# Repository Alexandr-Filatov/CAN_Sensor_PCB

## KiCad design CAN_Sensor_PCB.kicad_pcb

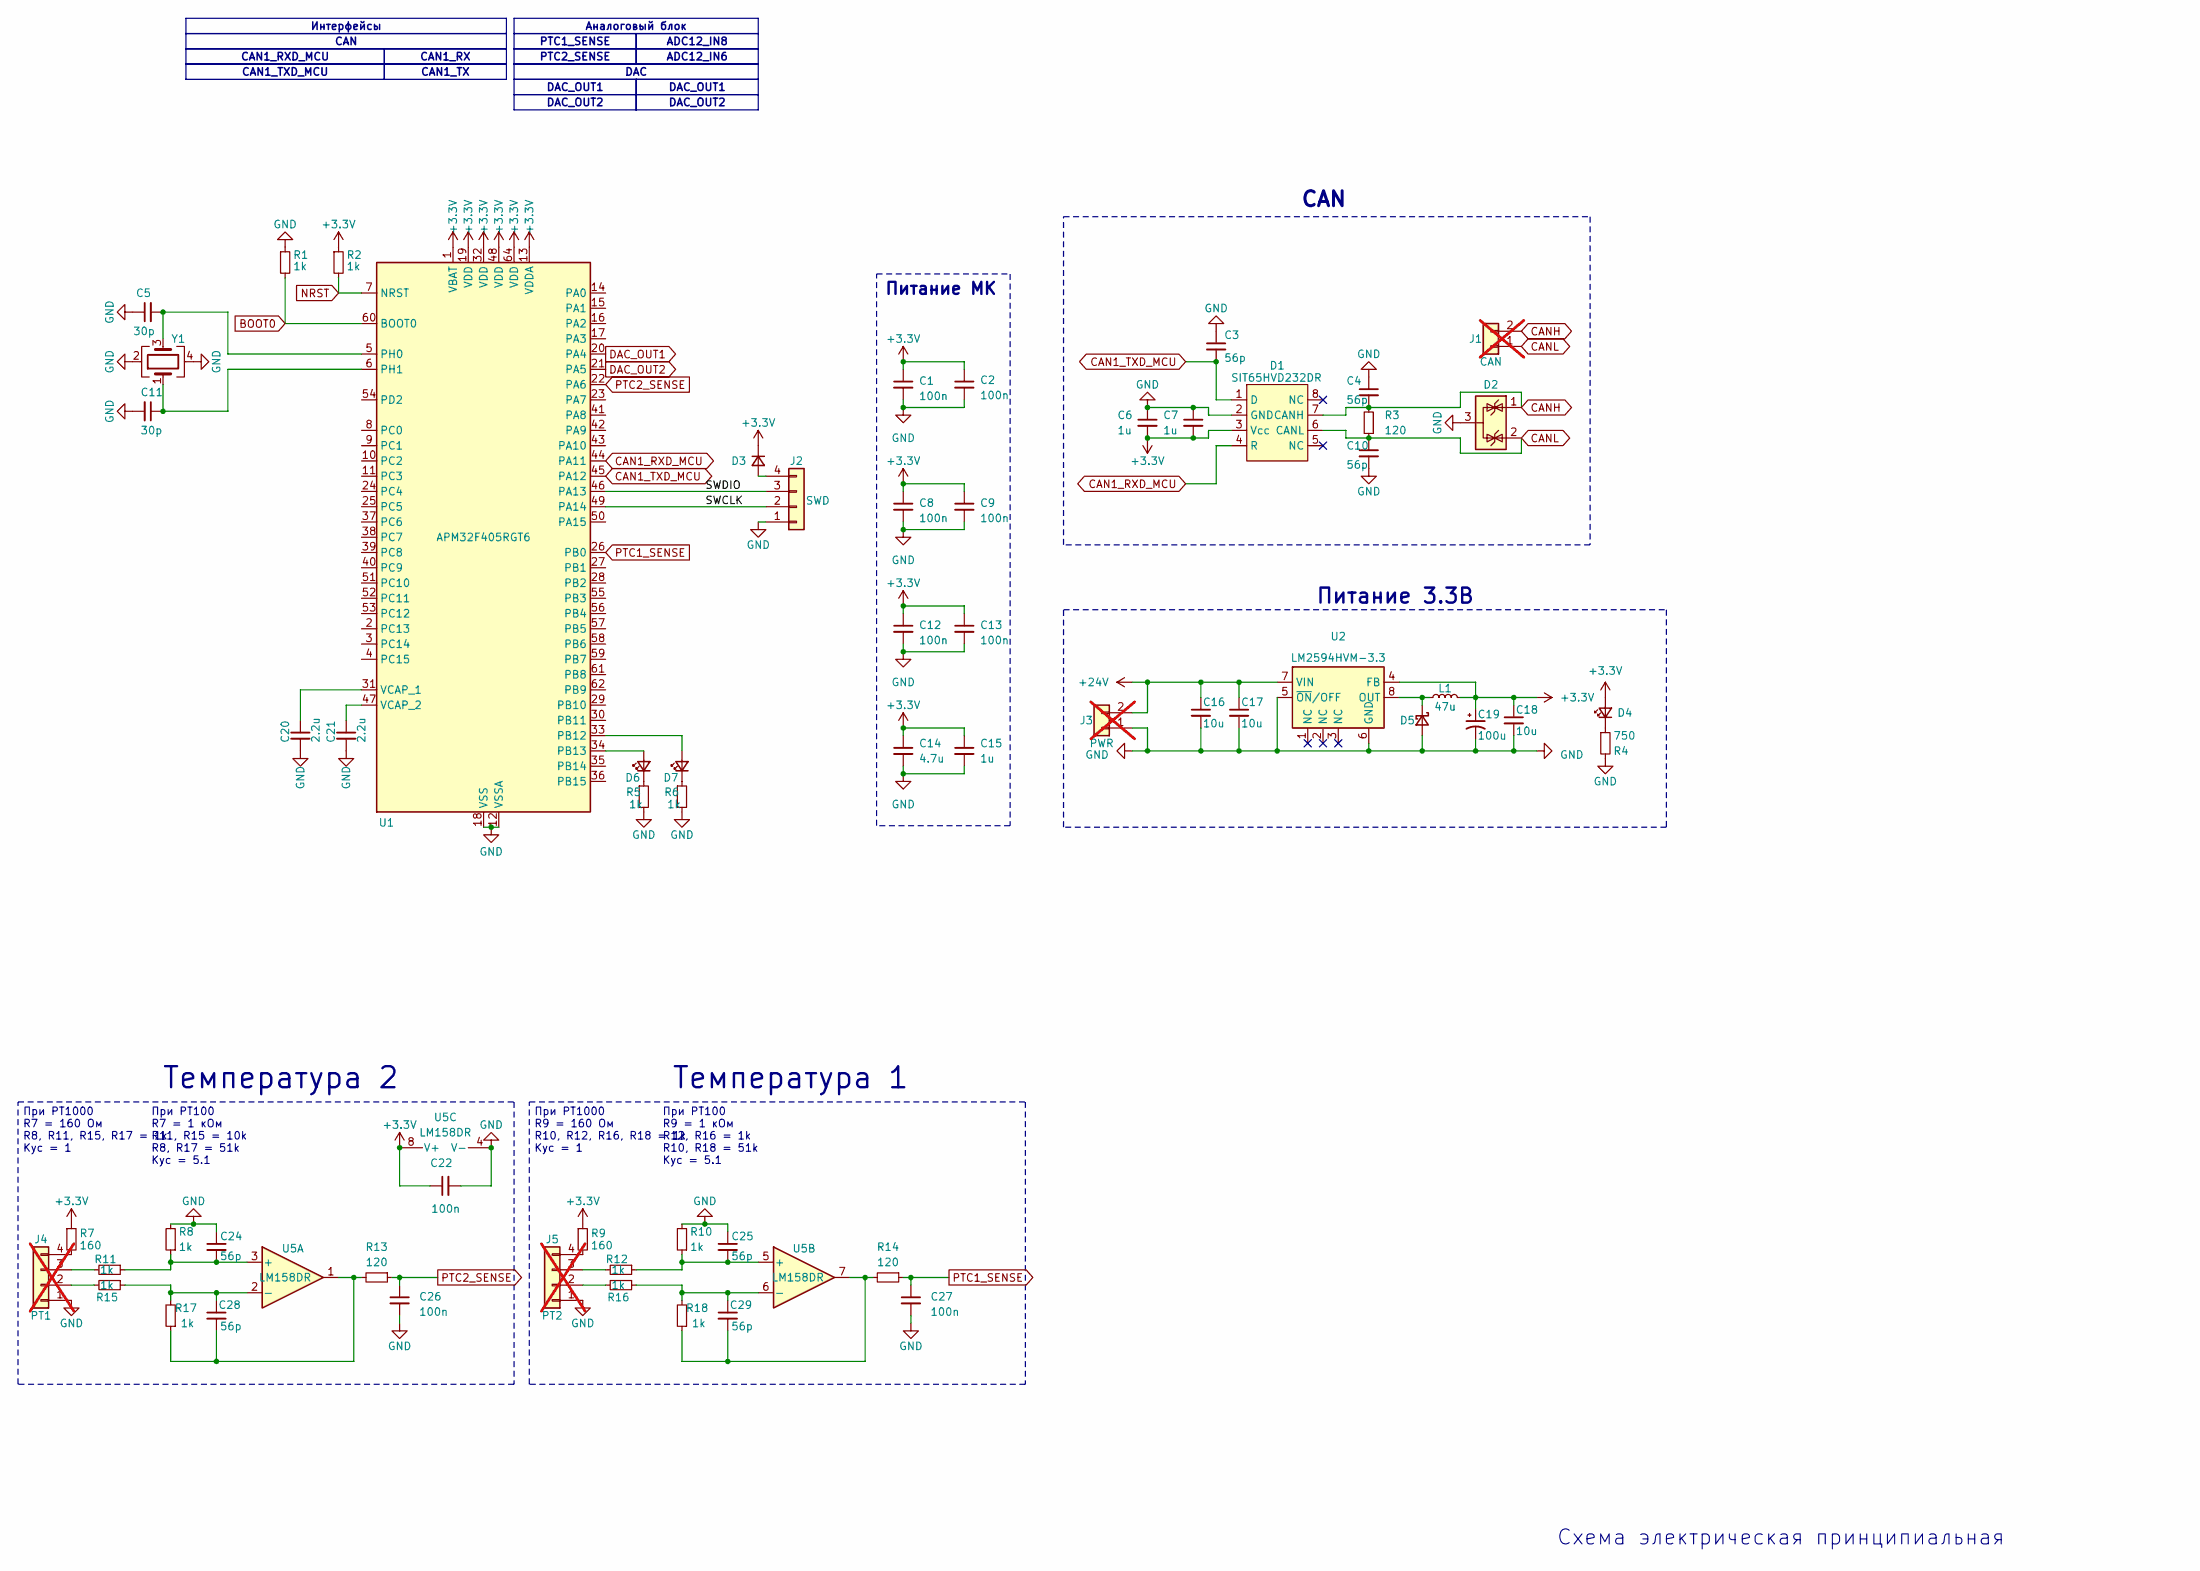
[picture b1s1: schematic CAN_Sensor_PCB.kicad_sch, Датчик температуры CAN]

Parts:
C1, C2, C8, C9, C12, C13, C22, C26, C27: 100n; C_0805_2012Metric_Pad1.18x1.45mm_HandSolder
C3, C4, C10, C24, C25, C28, C29: 56p; C_0805_2012Metric_Pad1.18x1.45mm_HandSolder
C5, C11: 30p; C_0805_2012Metric_Pad1.18x1.45mm_HandSolder
C6, C7, C15: 1u; C_0805_2012Metric_Pad1.18x1.45mm_HandSolder
C14: 4.7u; C_0805_2012Metric_Pad1.18x1.45mm_HandSolder
C16, C17, C18: 10u; C_1210_3225Metric_Pad1.33x2.70mm_HandSolder
C19: 100u; CP_EIA-3528-21_Kemet-B_HandSolder
C20, C21: 2.2u; C_0805_2012Metric_Pad1.18x1.45mm_HandSolder
D1: SOIC-8_3.9x4.9mm_P1.27mm
D2: SOT-23
D3: D_SOD-323_HandSoldering
D4, D6, D7: LED_0805_2012Metric
D5: D_SMA
J1, J3: Wire_1.5mm; not fitted
J2: PinHeader_1x04_P2.54mm_Vertical
J4, J5: Wire_1.5mm x 4; not fitted
L1: 47u; L_1812_4532Metric_Pad1.30x3.40mm_HandSolder
R1, R2, R5, R6, R8, R10, R11, R12, R15, R16, R17, R18: 1k; R_0805_2012Metric_Pad1.20x1.40mm_HandSolder
R3, R13, R14: 120; R_0805_2012Metric_Pad1.20x1.40mm_HandSolder
R4: 750; R_0805_2012Metric_Pad1.20x1.40mm_HandSolder
R7, R9: 160; R_0805_2012Metric_Pad1.20x1.40mm_HandSolder
U1: LQFP-64_10x10mm_P0.5mm
U2: SOIC-8_3.9x4.9mm_P1.27mm
U5: SO-8_3.9x4.9mm_P1.27mm
Y1: Crystal_SMD_SeikoEpson_FA238-4Pin_3.2x2.5mm

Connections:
+3.3V: C1.1, C2.1, C6.2, C7.2, C8.1, C9.1, C12.1, C13.1, C14.1, C15.1, C18.1, C19.1, C22.1, D1.3 (Vcc), D3.1 (K), D4.2 (A), L1.2, R2.1, R7.1, R9.1, U1.1 (VBAT), U1.13 (VDDA), U1.19 (VDD), U1.32 (VDD), U1.48 (VDD), U1.64 (VDD), U2.4 (FB), U5.8 (V+)
+24V: C16.1, C17.1, J3.2, U2.7 (VIN)
/SWCLK: J2.2, U1.49 (PA14)
/SWDIO: J2.3, U1.46 (PA13)
BOOT0: R1.2, U1.60 (BOOT0)
CAN1_RXD_MCU: D1.4 (R), U1.44 (PA11)
CAN1_TXD_MCU: C3.2, D1.1 (D), U1.45 (PA12)
CANH: C4.2, D1.7 (CANH), D2.1 (K), J1.2, R3.2
CANL: C10.1, D1.6 (CANL), D2.2 (K), J1.1, R3.1
DAC_OUT1: U1.20 (PA4)
DAC_OUT2: U1.21 (PA5)
GND: C1.2, C2.2, C3.1, C4.1, C5.1, C6.1, C7.1, C8.2, C9.2, C10.2, C11.2, C12.2, C13.2, C14.2, C15.2, C16.2, C17.2, C18.2, C19.2, C20.2, C21.2, C22.2, C24.1, C25.1, C26.2, C27.2, D1.2 (GND), D2.3 (A), D5.2 (A), J2.1, J3.1, J4.1, J5.1, R1.1, R4.2, R5.2, R6.2, R8.2, R10.2, U1.12 (VSSA), U1.18 (VSS), U1.63 (VSS), U2.5 (~ON/OFF), U2.6 (GND), U5.4 (V-), Y1.2, Y1.4
NRST: R2.2, U1.7 (NRST)
unnamed: C28.2, R13.2, R17.1, U5.1
unnamed: C29.2, R14.2, R18.1, U5.7
unnamed: D3.2 (A), J2.4
unnamed: D4.1 (K), R4.1
unnamed: D5.1 (K), L1.1, U2.8 (OUT)
unnamed: D6.2 (A), U1.34 (PB13)
unnamed: D6.1 (K), R5.1
unnamed: D7.2 (A), U1.33 (PB12)
unnamed: D7.1 (K), R6.1
unnamed: J4.2, R15.2
unnamed: J4.3, R11.2
unnamed: J4.4, R7.2
unnamed: J5.2, R16.2
unnamed: J5.3, R12.2
unnamed: J5.4, R9.2
unnamed: C5.2, U1.5 (PH0), Y1.3
unnamed: C11.1, U1.6 (PH1), Y1.1
unnamed: C20.1, U1.31 (VCAP_1)
unnamed: C21.1, U1.47 (VCAP_2)
unnamed: C24.2, R8.1, R11.1, U5.3 (+)
unnamed: C28.1, R15.1, R17.2, U5.2 (-)
unnamed: C25.2, R10.1, R12.1, U5.5 (+)
unnamed: C29.1, R16.1, R18.2, U5.6 (-)
PTC1_SENSE: C27.1, R14.1, U1.26 (PB0)
PTC2_SENSE: C26.1, R13.1, U1.22 (PA6)

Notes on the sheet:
Кус = 5.1
При PT1000
R10, R12, R16, R18 = 1k
R7 = 160 Ом
Схема электрическая принципиальная
R8, R17 = 51k
R9 = 160 Ом
Температура 2
R12, R16 = 1k
Питание МК
Температура 1
Питание 3.3В
R7 = 1 кОм
R9 = 1 кОм
R11, R15 = 10k
При PT100
CAN
Кус = 1
R10, R18 = 51k
R8, R11, R15, R17 = 1k
DAC_OUT2
CAN1_RX
DAC_OUT1
PTC1_SENSE
CAN1_TXD_MCU
CAN1_TX
DAC_OUT2
ADC12_IN6
PTC2_SENSE
CAN1_RXD_MCU
Интерфейсы
DAC
Аналоговый блок
ADC12_IN8

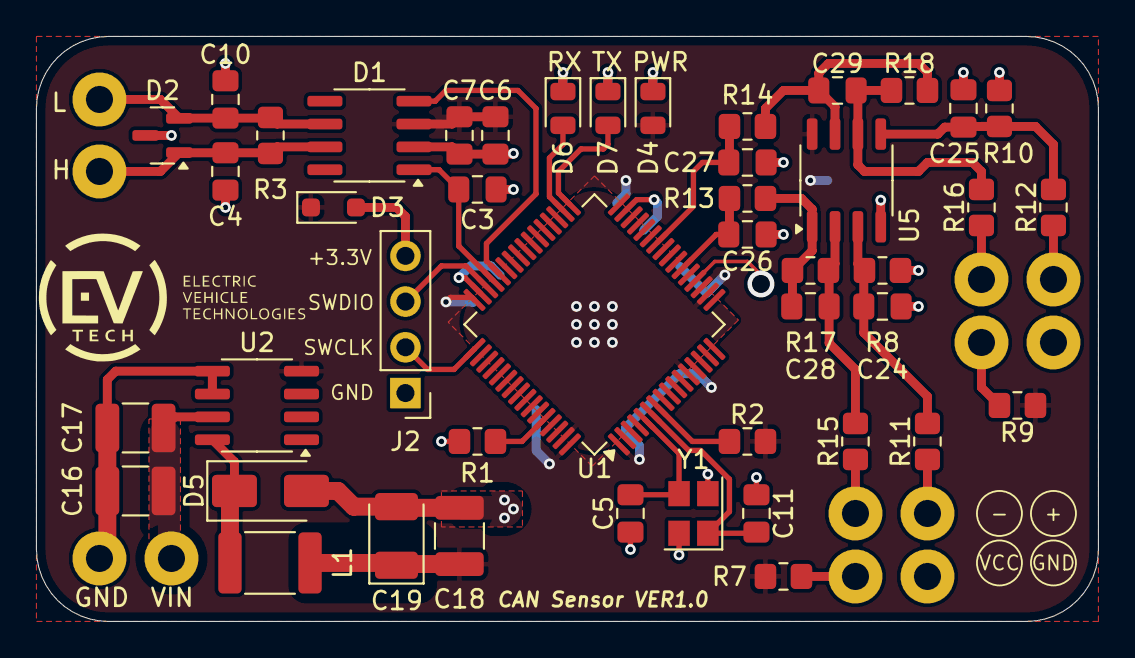
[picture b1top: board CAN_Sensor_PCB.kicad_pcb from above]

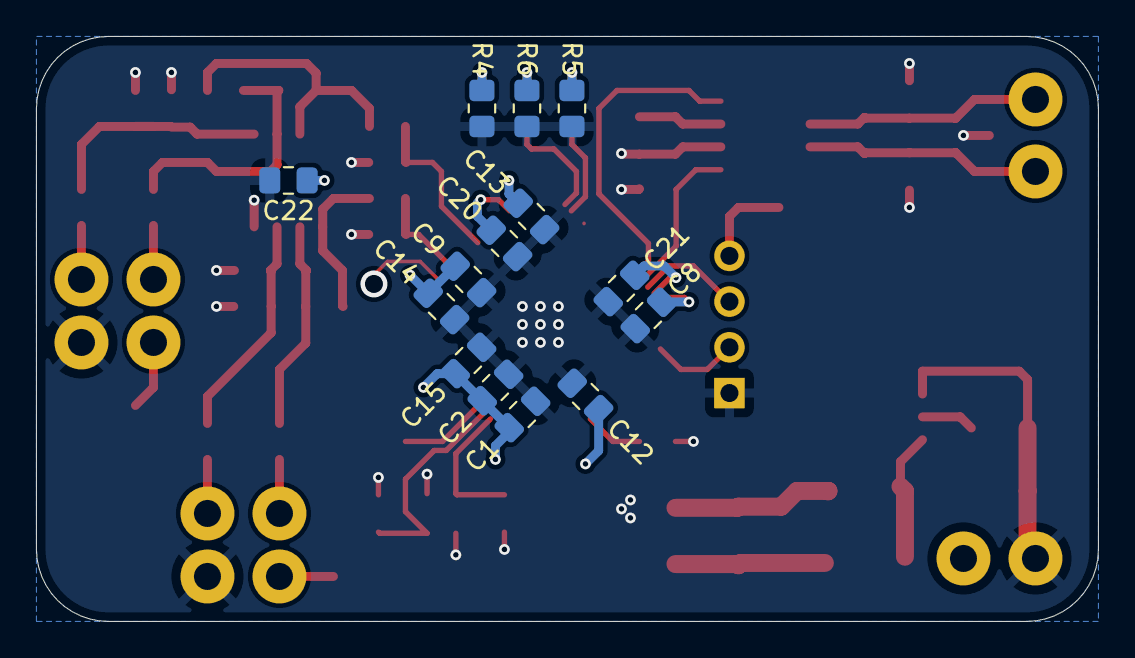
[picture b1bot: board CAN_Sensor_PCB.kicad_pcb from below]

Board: 2 copper layers, 59.0 x 32.5 mm, 63 parts (14 on the bottom side), 36 nets.

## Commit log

2025-04-19 zero commit
2025-04-20 VER1.0: заменил два усилителя на один
2025-04-20 VER1.0: отправил в резонит
2025-04-21 VER1.0: добавил BOM и закупочный лист
2025-06-19 VER1.0: добавил схему по госту в доки
2025-06-19 VER1.0: добавил спецификацию,3D, СБ в доки
2025-06-20 VER1.0: изменил спецификацию и рамку у СБ
2025-07-04 VER1.0: исправил СБ
2025-07-09 VER1.0: изменил вес линий в СБ
2025-07-10 VER1.0: изменил децимальники
2025-07-10 VER1.0: исправил Э3
2025-07-10 VER1.0: исправил Э3 еще раз
2025-07-14 VER21.0: исправил Э3
2025-07-15 VER1.0: переделал спецификацию в автокаде
2025-09-04 VER1.0: исправил номиналы резисторов для датчика и BOM
2025-09-04 VER1.0: добавил матлаб модель с температурным контуром
